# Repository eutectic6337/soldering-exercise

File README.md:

# soldering-exercise
provide practice for novice solderers with several levels of difficulty

a single board with 2 alternative circuits:

- SAO connector/battery holder, 2 LEDs + 2 resistors

- trickier: SAO connector/battery holder, 555 timer + 2 capacitors + 4 resistors + 2 LEDs

with through-hole and surface-mount pads for each component

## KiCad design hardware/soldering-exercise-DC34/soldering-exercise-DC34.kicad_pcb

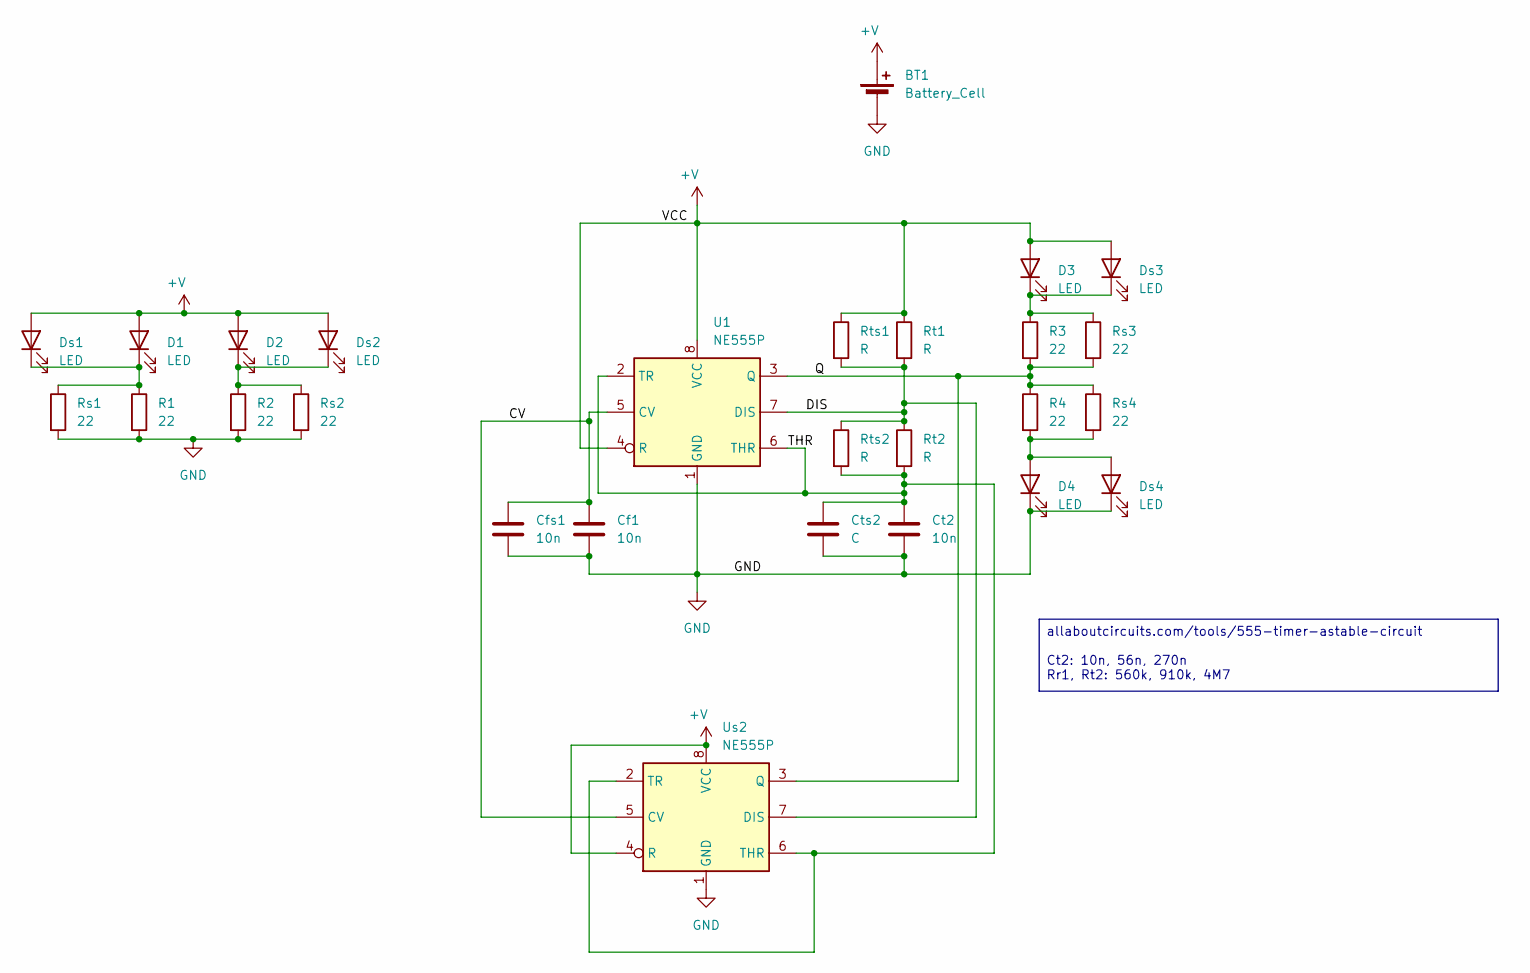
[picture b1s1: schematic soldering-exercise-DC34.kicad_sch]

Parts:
BT1: Battery_Cell; BatteryHolder_Multicomp_BC-2001_1x2032
Cf1: 10n; C_Rect_L7.0mm_W3.5mm_P5.00mm
Cfs1: 10n; C_1206_3216Metric_Pad1.33x1.80mm_HandSolder
Ct2: 10n; C_Rect_L7.0mm_W3.5mm_P5.00mm
Cts2: C; C_1206_3216Metric_Pad1.33x1.80mm_HandSolder
D1, D2, D3, D4: LED; LED_D5.0mm
Ds1, Ds2, Ds3, Ds4: LED; LED_1206_3216Metric_Pad1.42x1.75mm_HandSolder
R1, R2, R3, R4: 22; R_Axial_DIN0309_L9.0mm_D3.2mm_P12.70mm_Horizontal
Rs1, Rs2, Rs3, Rs4: 22; R_1206_3216Metric_Pad1.30x1.75mm_HandSolder
Rt1, Rt2: R; R_Axial_DIN0309_L9.0mm_D3.2mm_P12.70mm_Horizontal
Rts1, Rts2: R; R_1206_3216Metric_Pad1.30x1.75mm_HandSolder
U1: NE555P; DIP-8_W7.62mm
Us2: NE555P; SOIC-8_3.9x4.9mm_P1.27mm

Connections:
+V: BT1.1 (+), D1.2 (A), D2.2 (A), D3.2 (A), Ds1.2 (A), Ds2.2 (A), Ds3.2 (A), Rt1.1, Rts1.1, U1.4 (R), U1.8 (VCC), Us2.4 (R), Us2.8 (VCC); also elsewhere on the board
/CV: Cf1.1, Cfs1.1, U1.5 (CV), Us2.5 (CV)
/DIS: Rt1.2, Rt2.1, Rts1.2, Rts2.1, U1.7 (DIS), Us2.7 (DIS)
/Q: R3.2, R4.1, Rs3.2, Rs4.1, U1.3 (Q), Us2.3 (Q)
/THR: Ct2.1, Cts2.1, Rt2.2, Rts2.2, U1.2 (TR), U1.6 (THR), Us2.2 (TR), Us2.6 (THR)
GND: BT1.2 (-), Cf1.2, Cfs1.2, Ct2.2, Cts2.2, D4.1 (K), Ds4.1 (K), R1.2, R2.2, Rs1.2, Rs2.2, U1.1 (GND), Us2.1 (GND)
unnamed: D1.1 (K), Ds1.1 (K), R1.1, Rs1.1
unnamed: D2.1 (K), Ds2.1 (K), R2.1, Rs2.1
unnamed: D3.1 (K), Ds3.1 (K), R3.1, Rs3.1
unnamed: D4.2 (A), Ds4.2 (A), R4.2, Rs4.2

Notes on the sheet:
allaboutcircuits.com/tools/555-timer-astable-circuit Ct2: 10n, 56n, 270n Rr1, Rt2: 560k, 910k, 4M7

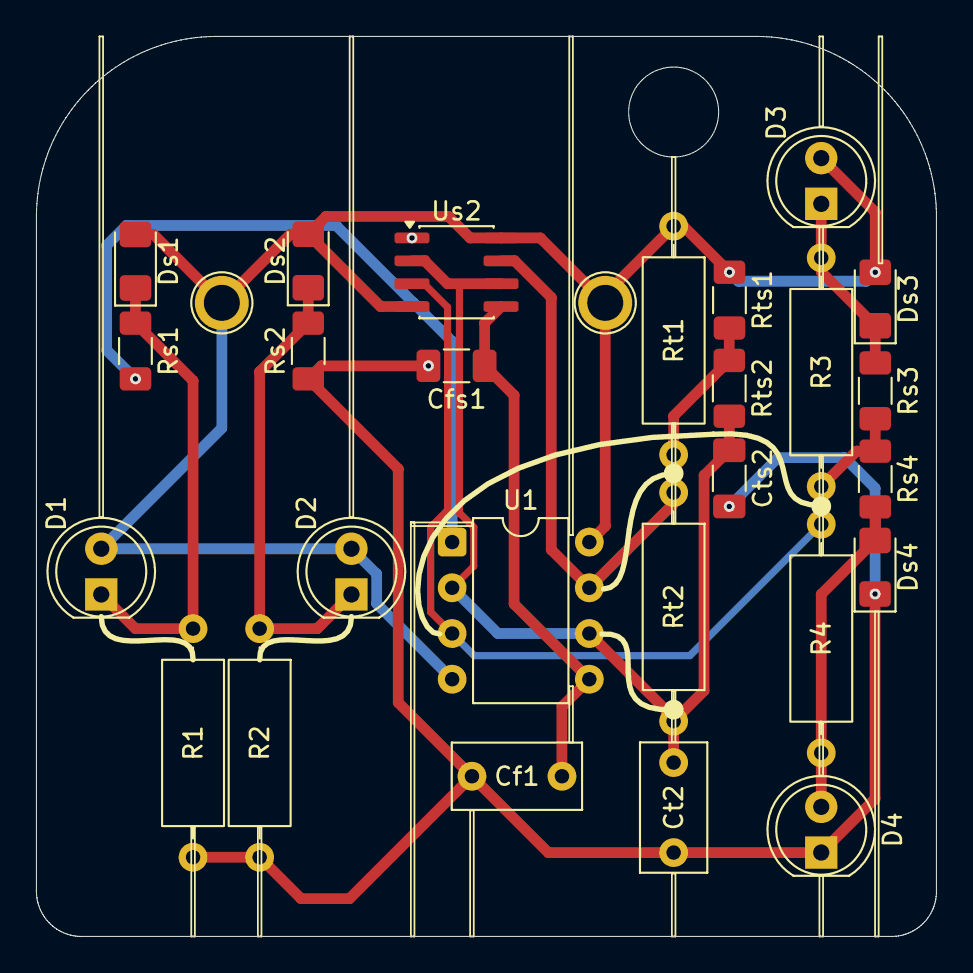
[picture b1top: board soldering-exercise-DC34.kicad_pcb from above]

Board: 2 copper layers, 50.0 x 50.0 mm, 30 parts (1 on the bottom side), 10 nets.

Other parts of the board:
V1, V1#2: TestPoint_Plated_Hole_D2.0mm
mount1: MountingHole_5mm

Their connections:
+V: V1.1, V1#2.1; also elsewhere on the board

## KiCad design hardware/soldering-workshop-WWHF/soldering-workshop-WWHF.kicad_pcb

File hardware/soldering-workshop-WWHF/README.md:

# WWHF 2026 soldering exercise

2 different circuits

through-hole, or surface-mount 1206 or 0603

## Simple circuit

2 LEDs light up whenever a battery is inserted

### part selection

2 LEDs of whichever colours you choose, for LED 1 and LED 2

- Red / Green / Yellow	1.8V..2.0V @ 20mA

- Blue / White	2.2V..2.4V @ 20mA

2 brightness-controlling resistors (one for each LED), for RES 1 and RES 2

- (V_battery - V_led) / I_led

    - e.g. (3 - 1.8(red)) / 0.02(bright) = 60 ohm

    - e.g. (3 - 2.4(white)) / 0.005(dim) = 30 ohm

- Recommendation: 30 ohm ... 300 ohm

1 battery holder

## more-complex circuit

555 timer astable multivibrator, alternates between 2 LEDs

### part selection

2 LEDs of whichever colours you choose, for LED 3 and LED 4

2 brightness-controlling resistors (one for each LED), for RES 3 and RES 4

1 555 timer IC

1 power-filtering capacitor, for CAP 12

- any value from 10nF up will be fine

- Recommendation: 10 nF ... 10 uF

1 timing-controlling capacitor, for CAP 11

- any value at all will work

- Recommendation: around 100 nF

2 timing-controlling resistors, for RES 11 and RES 12

- online calculator at https://allaboutcircuits.com/tools/555-timer-astable-circuit

- f = 1.44 / ((R_11 + 2 x R_12) x C_11)

    - T_high = 0.694 x (R_11 + R_12) x C_11

    - T_low = 0.694 x R_12 x C_11

    - e.g. f = 1.44 / ((100 + 2 x 900k) x 200n = 4 Hz, 50% duty

    - e.g. f = 1.44 / ((500k + 2 x 500k) x 100n = 9.6 Hz, 67% duty

- Recommendation: R_11 < 1 k ohm, R_12 > 500 k ohm

- Alternate: make R_11 significantly higher value to make flashing asymmetrical

1 battery holder, if your board does not yet have one

# identifying component values

## surface-mount resistors

Digits as read from the left give the value in ohms,
but the rightmost digit is the number of zeros to put onto the right.

- e.g. 104 = 10 0000 = 100 k ohms

- e.g. 562 = 56 00 = 5.6 k ohms

- e..g 470 = 47 ohms

## through-hole resistors

Colour bands from the left,
converted to digits, give the value in ohms,
but the rightmost band indicates the tolerance
and the second-rightmost band gives the number of zeros to put onto the right.

Ideally, there's a bigger gap between rightmost (tolerance) band and the others, to indicate orientation.
Or, the (left end of the) group of bands is closer to one end of the resistor body than the other.
But sometimes this can be hard to distinguish.
If you can't decide which of the colour bands is the right choice to start reading,
try reading it both ways. One way will give a "nonsense" value and the other way will be correct.

Or, just measure it with a multimeter - the official value will be whatever "preferred value" (see below) is closest to the measured value.

### [preferred values](https://en.wikipedia.org/wiki/E12_series)

Resistor values are only approximate (as indicated by their "tolerance"), and are only manufactured in a limited set of nominal values.
A "nonsense" value is any value that does not appear in that set - you will never find a standard resistor marked with a value outside that set.

| The "E12" series of values |
| --- |
| 1.0, 1.2, 1.5, 1.8, 2.2, 2.7, 3.3, 3.9, 4.7, 5.6, 6.8, 8.2 |

| The "E24" series of values |
| --- |
| 1.0, 1.1, 1.2, 1.3, 1.5, 1.6, 1.8, 2.0, 2.2, 2.4, 2.7, 3.0, 3.3, 3.6, 3.9, 4.3, 4.7, 5.1, 5.6, 6.2, 6.8, 7.5, 8.2, 9.1 |

### [colour code](https://en.wikipedia.org/wiki/Electronic_color_code)

Black = 0

Brown = 1

Red = 2

Orange = 3

Yellow = 4

Green = 5

Blue = 6

Violet or Purple = 7

Grey = 8

White = 9

Gold / Silver / Pink used for tolerance or obscure multiplier only

## examples

- e.g. Brown, Black, Yellow, tolerance... = 10 0000 = 100 k ohms

- e.g. Green, Blue, Red, tolerance... = 56 00 = 5.6 k ohms

- e..g Yello, Violet, Black, tolerance... = 47 ohms

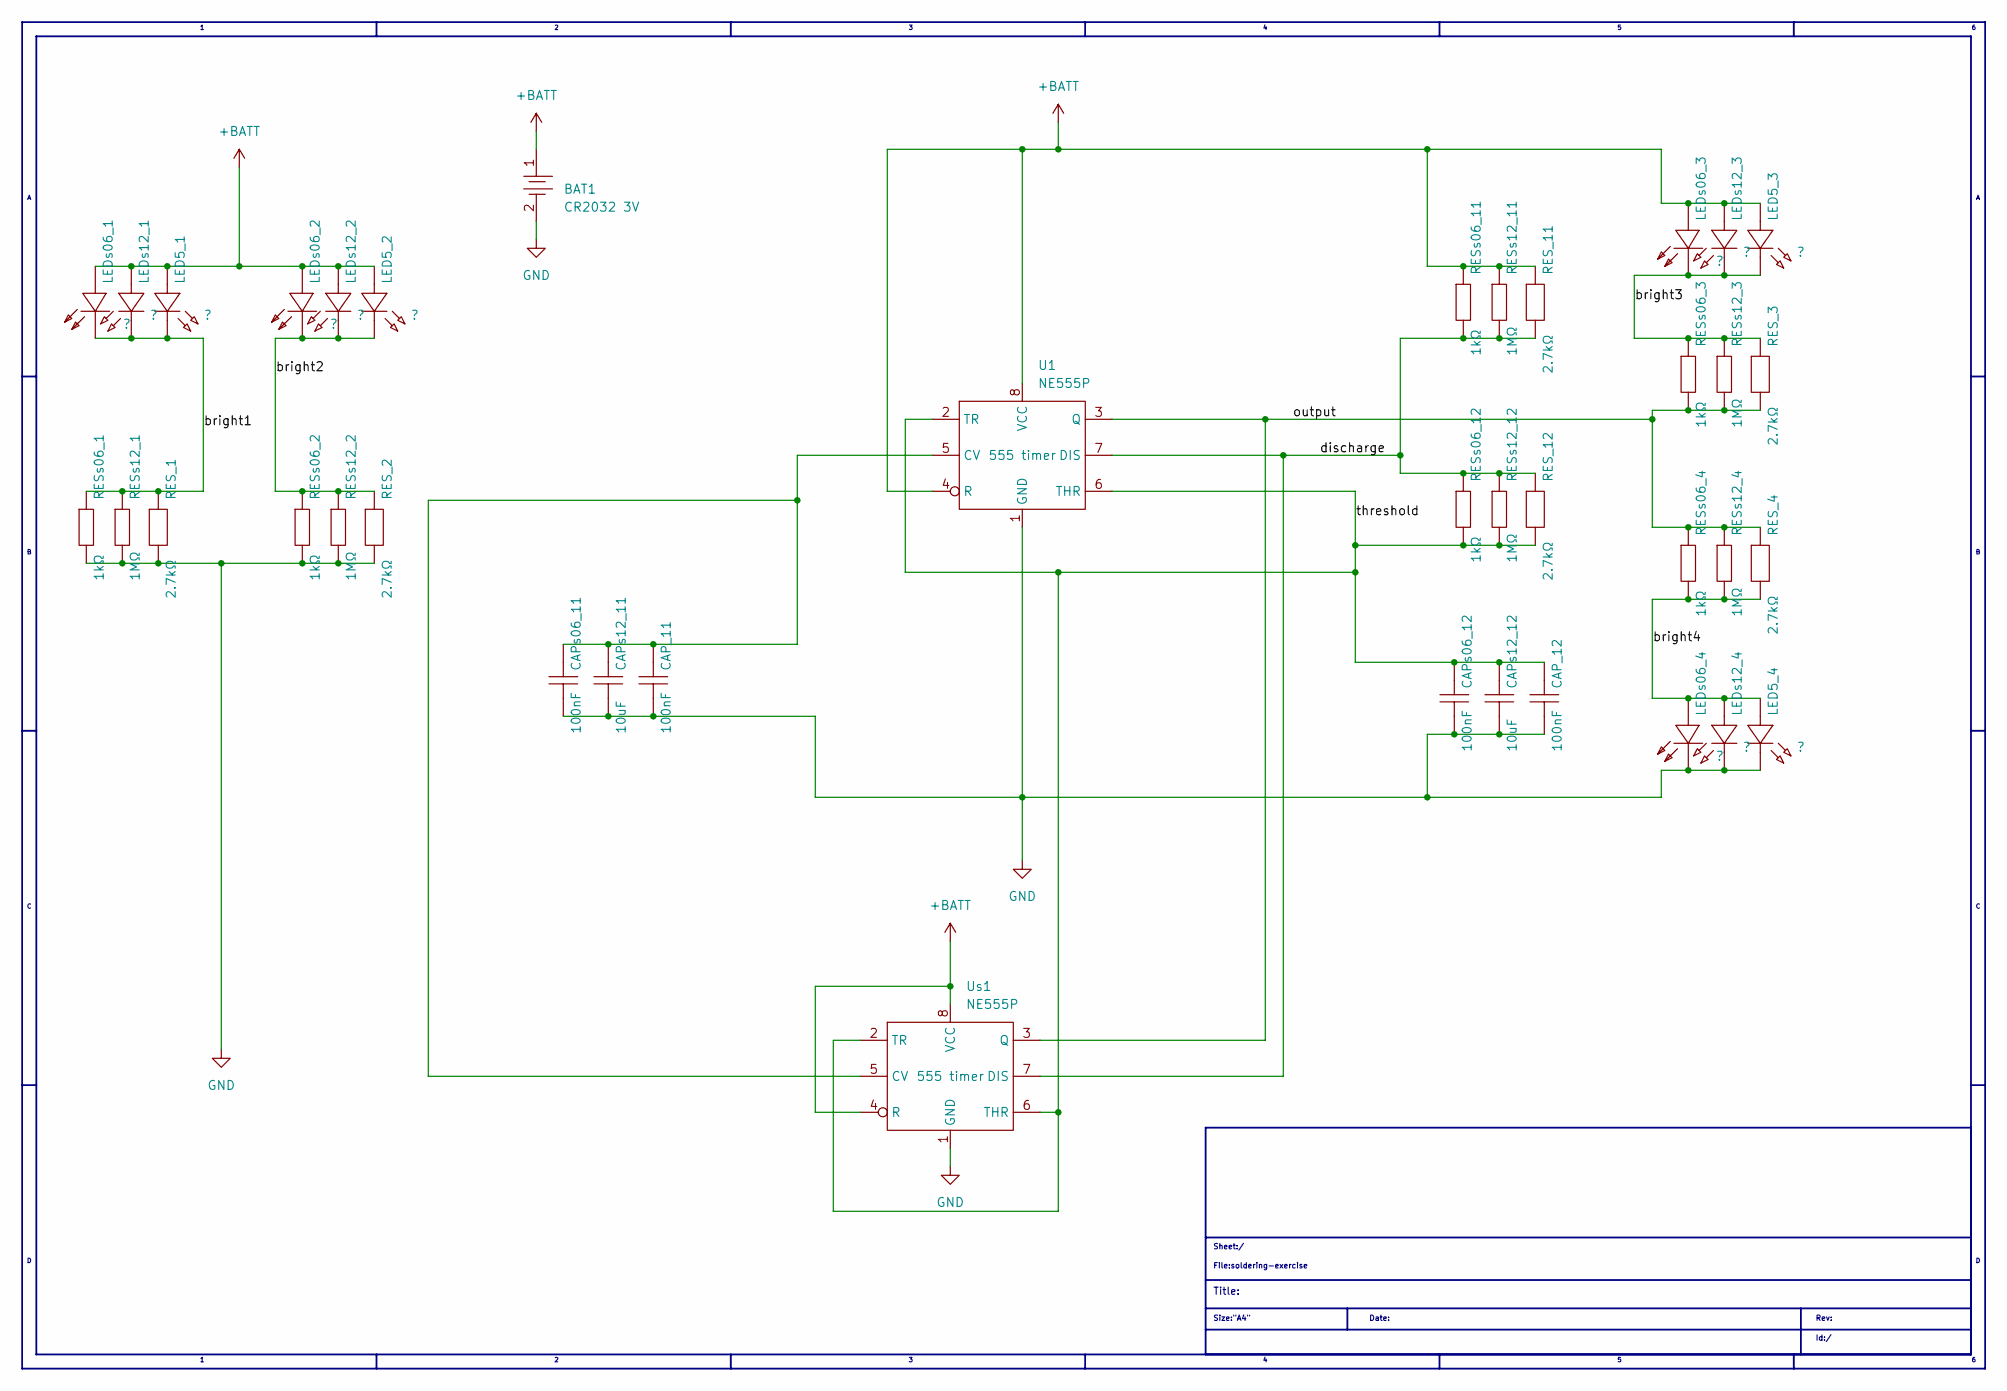
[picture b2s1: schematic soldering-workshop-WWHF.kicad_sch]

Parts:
BAT1: CR2032 3V; BatteryHolder_Multicomp_BC-2001_1x2032; MANUFACTURER PART CR2032弯脚电池片铜 3V; LCSC PART NAME CR2032弯脚电池片铜 3V
CAP_11, CAP_12: 100nF; C_Rect_L7.0mm_W2.5mm_P5.00mm; TOLERANCE ±10%; VOLTAGE RATING 310V; MANUFACTURER PART MX2104KQ3B30YB20TS1R; LCSC PART NAME 100nF ±10% 310V
CAPs06_11, CAPs06_12: 100nF; C_0603_1608Metric; TOLERANCE ±10%; VOLTAGE RATING 50V; MANUFACTURER PART CC0603KRX7R9BB104; LCSC PART NAME 100nF ±10% 50V
CAPs12_11, CAPs12_12: 10uF; C_1206_3216Metric; TOLERANCE ±10%; VOLTAGE RATING 50V; MANUFACTURER PART HGC1206R5106K500NSPJ; LCSC PART NAME 10uF ±10% 50V
LED5_1, LED5_2, LED5_3, LED5_4: ?; LED_D5.0mm; VOLTAGE - FORWARD(VF) 3.4V; MANUFACTURER PART DY-332SUGD-A3; LCSC PART NAME 5mm圆头有边翠绿色
LEDs06_1, LEDs06_2, LEDs06_3, LEDs06_4: ?; LED_0603_1608Metric; MANUFACTURER PART KT-0603R; LCSC PART NAME 0603 红灯 高亮
LEDs12_1, LEDs12_2, LEDs12_3, LEDs12_4: ?; LED_1206_3216Metric; VOLTAGE - FORWARD(VF) 1.8V~2.4V; MANUFACTURER PART P2-1206RTCS2-0.9T-F; LCSC PART NAME 红灯 反贴
RES_1, RES_2, RES_3, RES_4, RES_11, RES_12: 2.7kΩ; R_Axial_DIN0207_L6.3mm_D2.5mm_P10.16mm_Horizontal; TOLERANCE ±1%; MANUFACTURER PART MF0W4FF2701A50; LCSC PART NAME MF0W4FF2701A50
RESs06_1, RESs06_2, RESs06_3, RESs06_4, RESs06_11, RESs06_12: 1kΩ; R_0603_1608Metric; TOLERANCE ±1%; VOLTAGE-SUPPLY(MAX) 75V; MANUFACTURER PART 0603WAF1001T5E; LCSC PART NAME 1kΩ ±1% 100mW 厚膜电阻
RESs12_1, RESs12_2, RESs12_3, RESs12_4, RESs12_11, RESs12_12: 1MΩ; R_1206_3216Metric; TOLERANCE ±1%; VOLTAGE-SUPPLY(MAX) 200V; MANUFACTURER PART 1206W4F1004T5E; JLCPCB PART CLASS Basic Part
U1: 555 timer; DIP-8_W7.62mm
Us1: 555 timer; SOIC-8_3.9x4.9mm_P1.27mm

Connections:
+BATT: BAT1.1, LED5_1.1 (A), LED5_2.1 (A), LED5_3.1 (A), LEDs06_1.2 (A), LEDs06_2.2 (A), LEDs06_3.2 (A), LEDs12_1.2 (A), LEDs12_2.2 (A), LEDs12_3.2 (A), RES_11.2, RESs06_11.2, RESs12_11.2, U1.4 (R), U1.8 (VCC), Us1.4 (R), Us1.8 (VCC)
/bright1: LED5_1.2 (C), LEDs06_1.1 (K), LEDs12_1.1 (C), RES_1.2, RESs06_1.2, RESs12_1.2
/bright2: LED5_2.2 (C), LEDs06_2.1 (K), LEDs12_2.1 (C), RES_2.2, RESs06_2.2, RESs12_2.2
/bright3: LED5_3.2 (C), LEDs06_3.1 (K), LEDs12_3.1 (C), RES_3.2, RESs06_3.2, RESs12_3.2
/bright4: LED5_4.1 (A), LEDs06_4.2 (A), LEDs12_4.2 (A), RES_4.1, RESs06_4.1, RESs12_4.1
/discharge: RES_11.1, RES_12.2, RESs06_11.1, RESs06_12.2, RESs12_11.1, RESs12_12.2, U1.7 (DIS), Us1.7 (DIS); also elsewhere on the board
/output: RES_3.1, RES_4.2, RESs06_3.1, RESs06_4.2, RESs12_3.1, RESs12_4.2, U1.3 (Q), Us1.3 (Q); also elsewhere on the board
/threshold: CAP_12.2, CAPs06_12.2, CAPs12_12.2, RES_12.1, RESs06_12.1, RESs12_12.1, U1.2 (TR), U1.6 (THR), Us1.2 (TR), Us1.6 (THR); also elsewhere on the board
GND: BAT1.2, CAP_11.1, CAP_12.1, CAPs06_11.1, CAPs06_12.1, CAPs12_11.1, CAPs12_12.1, LED5_4.2 (C), LEDs06_4.1 (K), LEDs12_4.1 (C), RES_1.1, RES_2.1, RESs06_1.1, RESs06_2.1, RESs12_1.1, RESs12_2.1, U1.1 (GND), Us1.1 (GND)
unnamed: CAP_11.2, CAPs06_11.2, CAPs12_11.2, U1.5 (CV), Us1.5 (CV)

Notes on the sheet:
Rev:
Sheet:/
Id:/
Date:
Size:"A4"
Title:
File:soldering-exercise

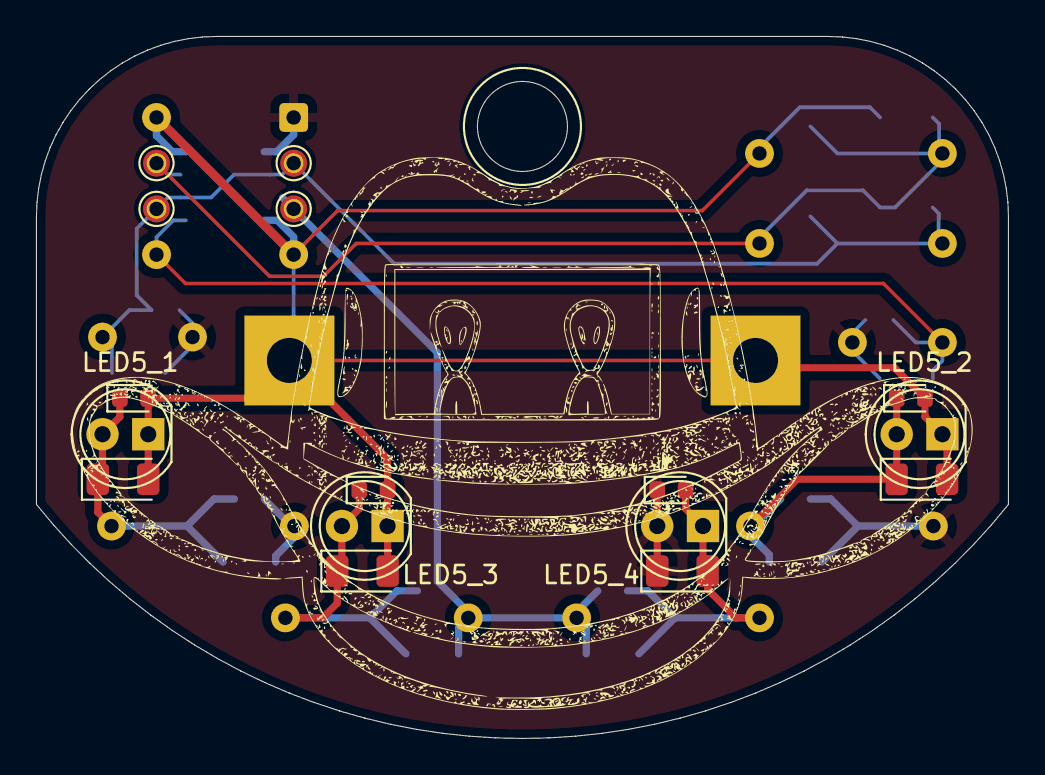
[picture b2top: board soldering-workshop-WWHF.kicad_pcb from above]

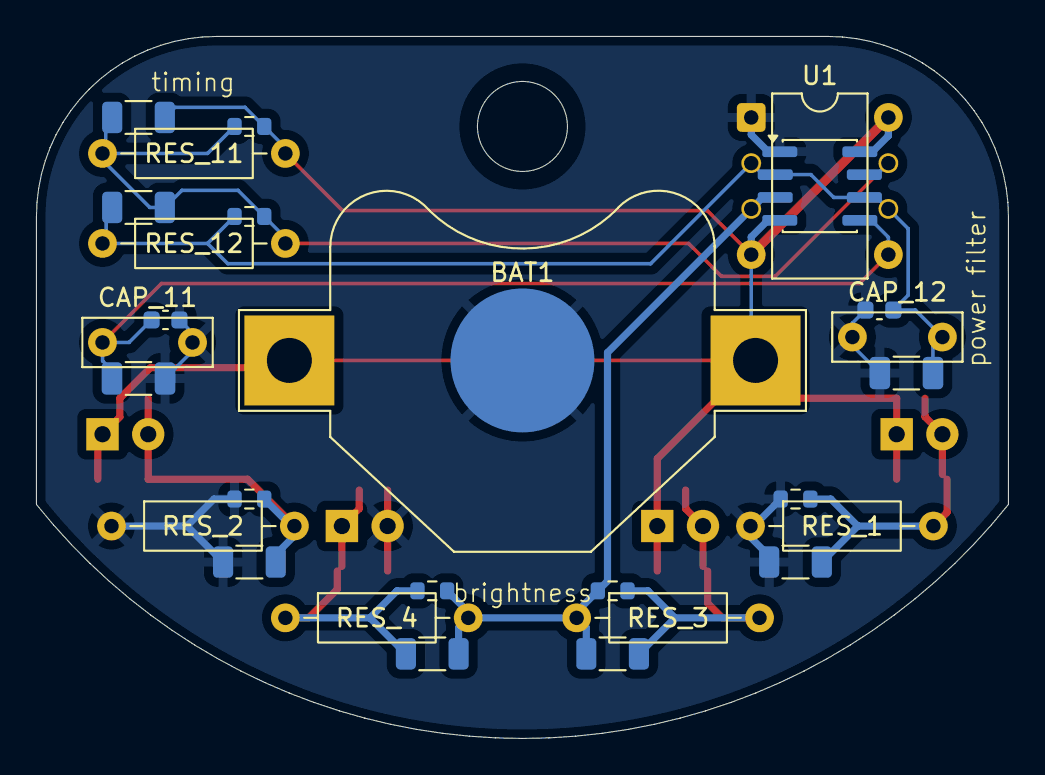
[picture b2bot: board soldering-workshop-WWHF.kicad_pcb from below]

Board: 2 copper layers, 54.0 x 39.0 mm, 44 parts (27 on the bottom side), 10 nets.

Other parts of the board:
U1p2, U1p3, U1p6, U1p7: TestPoint_Pad_D1.5mm
lanyard: TestPoint_Plated_Hole_D5.0mm

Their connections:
/discharge: U1p7.1; also elsewhere on the board
/output: U1p3.1; also elsewhere on the board
/threshold: U1p2.1, U1p6.1; also elsewhere on the board

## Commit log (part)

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2025-10-08 flesh out description
2025-10-08 create schematic
2025-10-08 add footprints
2025-10-08 start placing components
2025-10-08 duplicate THT to SMD, layout board
2025-10-08 document values
2025-10-08 added PhreakNIC logo
2025-10-28 added images
2025-12-28 re-layout for WWHF
2025-12-28 tweak Markdown
2025-12-28 add description of alternates
2025-12-28 add quick guide to reading values
2025-12-28 fight with Markdown
2025-12-28 maybe this'll look OK
2025-12-28 done with resistors
2025-12-28 add 555 link
2025-12-29 add recommended values
